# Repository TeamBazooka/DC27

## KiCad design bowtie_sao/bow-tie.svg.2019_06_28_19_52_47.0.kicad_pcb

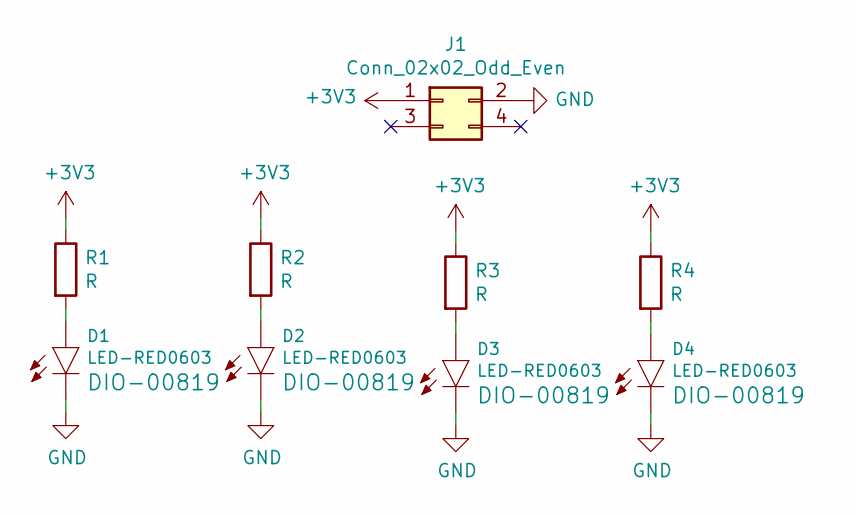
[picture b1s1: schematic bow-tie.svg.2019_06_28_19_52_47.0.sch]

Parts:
D1, D2, D3, D4: LED-RED0603; LED-0603
J1: Conn_02x02_Odd_Even; 2X3
R1, R2, R3, R4: R; 0603

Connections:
+3V3: J1.1, R1.1, R2.1, R3.1, R4.1
GND: D1.C, D2.C, D3.C, D4.C, J1.2
unnamed: D1.A, R1.2
unnamed: D2.A, R2.2
unnamed: D3.A, R3.2
unnamed: D4.A, R4.2

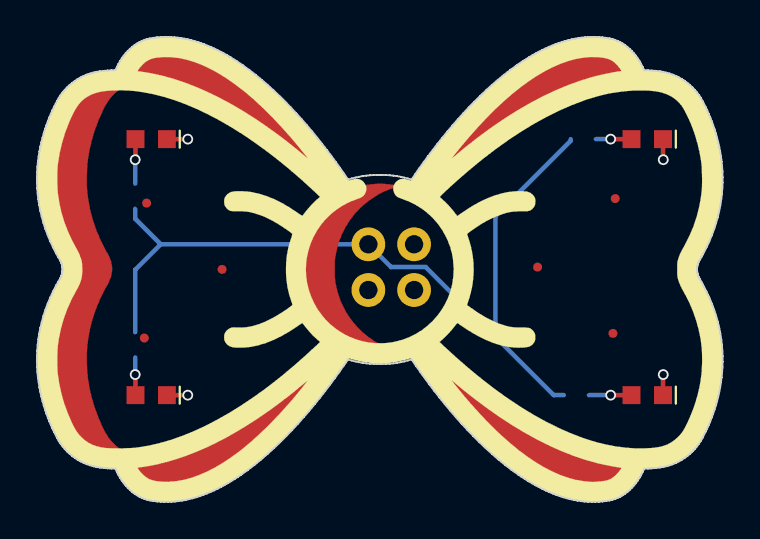
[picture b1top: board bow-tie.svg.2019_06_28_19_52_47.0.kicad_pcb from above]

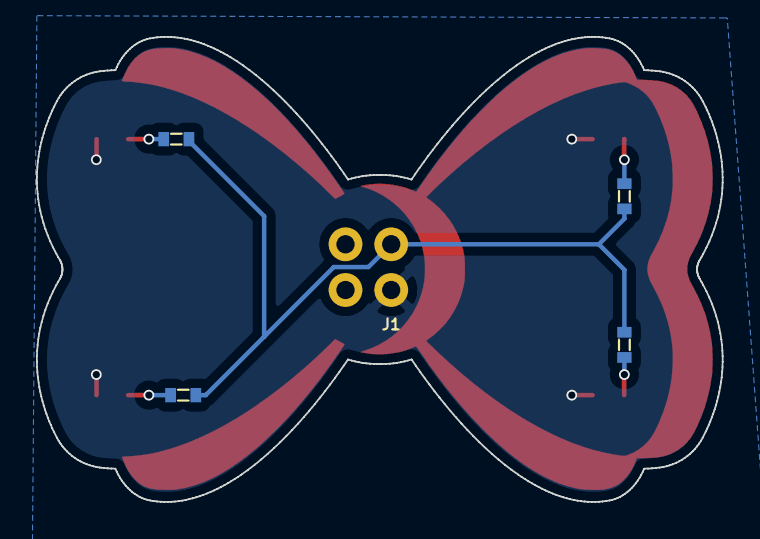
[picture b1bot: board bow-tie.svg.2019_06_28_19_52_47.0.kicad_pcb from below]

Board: 2 copper layers, 38.1 x 25.8 mm, 9 parts (5 on the bottom side), 6 nets.

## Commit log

2019-06-25 add components for board shape
2019-06-25 some fixes for fab
2019-06-26 Get the correct animation working and rtc alarm wake working
2019-06-26 artwork for cabase sao
2019-06-27 Symetric cylon
2019-06-27 Add rtc code to firmware
2019-06-27 Add shift registers to address more leds, should charlieplex
2019-06-27 Add board layout to kicad
2019-06-27 Shrink layout svg to 4"
2019-06-27 Rough layout, still need all tracks
2019-06-27 Add BOM and pdf schematic
2019-06-27 prot gerbers
2019-06-28 Add bom with pricing
2019-06-28 Layout all traces
2019-06-28 Remove via in pad
2019-06-28 bowtie art
2019-06-28 Some updates to the bom
2019-06-28 Add SAO to head
2019-06-29 Move some small traces a little, update BOMs
2019-06-29 Add bowtie SAO
2019-06-29 Firmware has correct pin for shift registers
2019-06-29 add some small silkscreen
2019-06-29 Some updates to poc
2019-06-29 Add cabage sao
2019-08-07 Add firmware that should work
2019-08-07 Download stm32flash automatically
2019-08-07 oh yeah, we had to put things in that order
2019-08-08 add readme
